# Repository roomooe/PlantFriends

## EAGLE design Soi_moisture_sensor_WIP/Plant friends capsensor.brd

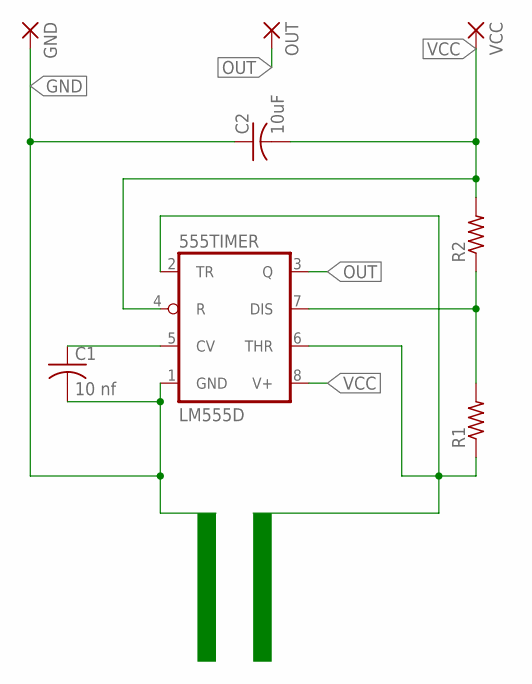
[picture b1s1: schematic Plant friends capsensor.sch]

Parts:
555TIMER: LM555D; SO08
C1: 10 nf; C0805
C2: 10uF; C0805
GND: WIREPAD2,54/1,0; 2,54/1,0
OUT: WIREPAD2,54/1,0; 2,54/1,0
R1, R2: R-US_R0805; R0805
VCC: WIREPAD2,54/1,0; 2,54/1,0

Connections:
C: 555TIMER.2 (TR), 555TIMER.6 (THR), R1.1
GND: 555TIMER.1 (GND), C1.2, C2.1, GND.1
unnamed: 555TIMER.7 (DIS), R1.2, R2.1
unnamed: 555TIMER.5 (CV), C1.1
OUT: 555TIMER.3 (Q), OUT.1
VCC: 555TIMER.4 (R), 555TIMER.8 (V+), C2.2, R2.2, VCC.1

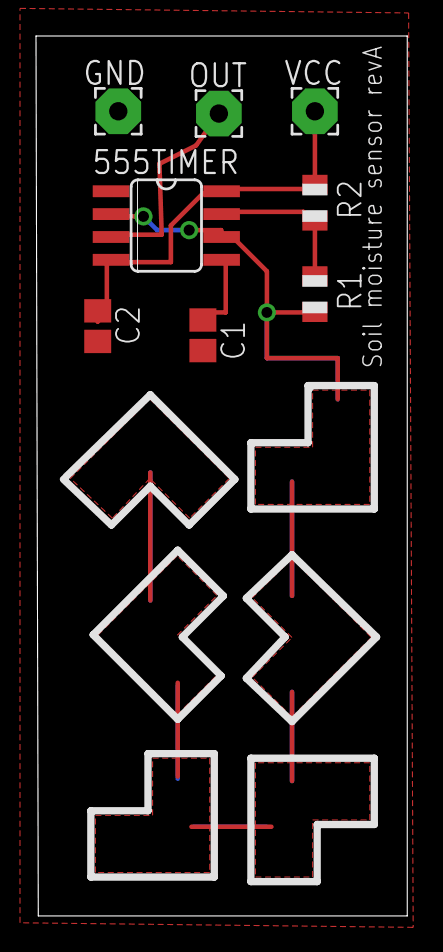
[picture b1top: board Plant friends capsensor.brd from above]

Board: 2 copper layers, 20.6 x 48.9 mm, 8 parts (0 on the bottom side), 6 nets.

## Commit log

2015-01-20 Android app
    Redesigned the android app and added stretch feature of the GUI (very
    ugly and manual)
2015-01-21 RFM69w support
    Rewrote sensor_node.ino and gateway.ino for RFM69w transceiver. Might
    need to tweek ACK a little...
2015-02-09 New soilmoisturesensors
    Added capacitance soil moisture sensors and base unit enclosure
    No node support for soilmoisture snesor in node code yet
2015-05-27 Waterlevel sensor + bugs
    Removed batttery meter and replaced it water level sensor + fixed some
    minor bugs
2015-06-09 New enclosures for sensor node
